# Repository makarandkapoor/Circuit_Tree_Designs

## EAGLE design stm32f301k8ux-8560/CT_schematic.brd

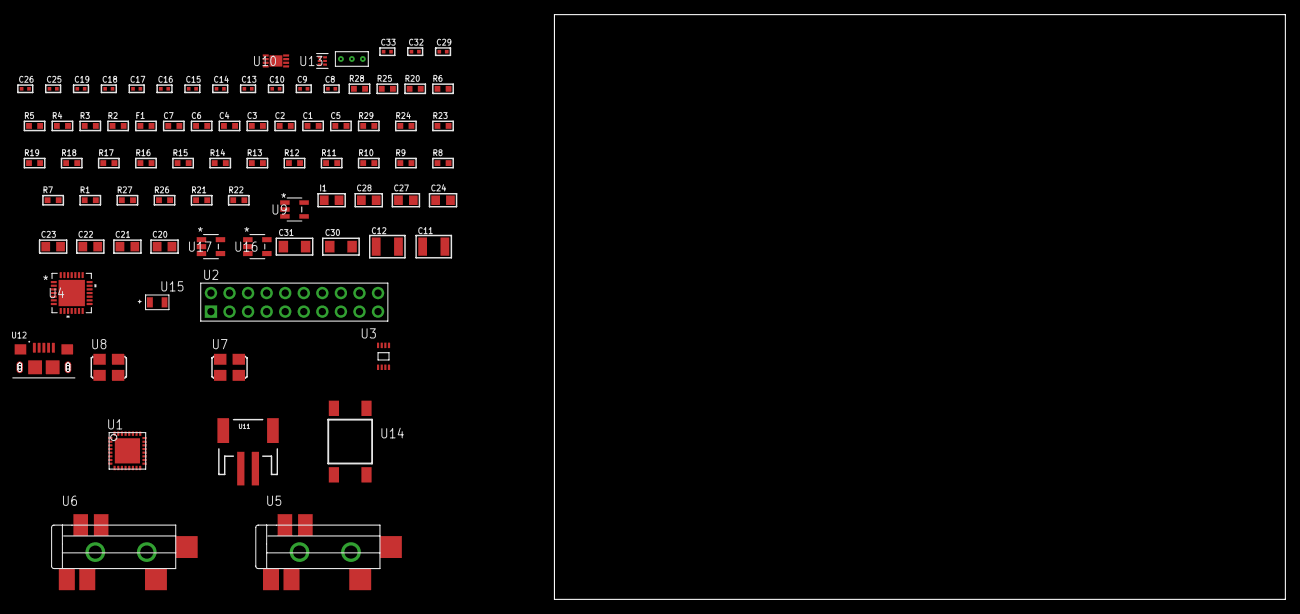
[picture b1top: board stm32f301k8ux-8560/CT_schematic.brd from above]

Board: 2 copper layers, 173.4 x 80.0 mm, 82 parts (0 on the bottom side), 41 nets, no tracks yet.

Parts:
C1, C2, C3, C4: 1e-07; C0603
C5: 4.7e-06; C0603
C6: 1e-08; C0603
C7: 1e-06; C0603
C8, C9, C15, C16, C17, C18, C19, C29: 1e-07; C0402
C10, C25, C26, C32, C33: 1e-08; C0402
C11, C12: 2.2e-05; C1210
C13, C14: 1e-09; C0402
C20, C21, C22, C23, C24, C27, C28: 1e-05; C0805
C30, C31: 1e-05; C1206
F1: 240.0; L0603
I1: 2.2e-06; L0805
R1, R7, R8, R9, R10, R11, R12, R13, R14, R15, R16, R23, R24, R29: 10000.0; R0603
R2: 1000.0; R0603
R3: 1600.5; R0603
R4: 4700.0; R0603
R5, R6: 2200.0; R0603
R17, R18, R19: 47000.0; R0603
R20: 680.0; R0603
R21: 220000.0; R0603
R22: 1000000.0; R0603
R25: 9100.0; R0603
R26: 680000.0; R0603
R27: 120000.0; R0603
R28: 2000.0; R0603
U1: STM32F301K8U7; UFQFPN32
U2: TST-110-05-T-D-RA
U3: 24AA64T-I/MNY; TDFN-8/6MM
U4: WM8731CLSEFL; QFN-28
U5, U6: SJ-43515TS-SMT-TR
U7: ASFL1-12.288MHZ-EC-T; ASFL1
U8: ASFL1-25MHZ-NCS; ASFL1
U9: ltc3406es5; TSOT-23-5
U10: MCP73831T-2ACI/MC; DFN8_2X3MC
U11: S2B-PH-SM4-TB(LF)(SN); JST-2-SMD
U12: 10118193-0001LF; FCI_10118193-0001LF
U13: TPS3895ADRYR; SON-6
U14: 4-1437565-2; SW_4-1437565-2
U15: Q65110A2395; LGM67K-G1J2-24-Z
U16, U17: nc7sz125m5x; NC7SZ125M5X
U18: Dummy; DUMMY_PACKAGE_174

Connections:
CLK_U1_2: U1.2, U8.3
CLK_U4_1: U4.1, U7.3
GND: C1.2, C2.2, C3.2, C4.2, C5.2, C6.2, C7.2, C8.2, C9.2, C10.2, C14.2, C15.2, C16.2, C17.2, C18.2, C19.2, C20.2, C21.2, C22.2, C23.2, C24.2, C25.2, C26.2, C27.2, C28.1, C28.2, C29.2, C30.2, C31.2, C32.2, C33.2, R2.2, R7.2, R13.2, R14.2, R15.2, R17.2, R18.2, R19.2, R21.2, R25.2, R27.2, R28.2, U1.6, U1.16, U1.32, U1.EPAD, U2.4, U2.6, U2.8, U2.10, U2.12, U2.14, U2.16, U2.18, U2.20, U3.4, U3.7, U4.4, U4.15, U4.19, U4.25, U4.26, U4.29, U5.1, U6.1, U7.2, U8.2, U9.2, U10.6, U10.9, U11.2, U12.5, U12.6, U12.7, U12.8, U12.9, U13.2, U15.C, U16.2, U16.3, U17.1, U17.3, U18.1
INPUT_USBPOWER_5V: C30.1, R29.2, U10.1, U10.2, U12.1
NET_U1_4: R4.1, U1.4, U17.4
NET_U1_5: C6.1, C7.1, F1.1, U1.5
NET_U1_22: R3.1, U1.22, U15.A
NET_U1_28: R1.1, U1.28, U14.3, U14.4
NET_U1_29: R5.1, U1.29, U3.6
NET_U1_30: R6.1, U1.30, U3.5
NET_U1_31: R7.1, U1.31
NET_U2_19: R13.1, U2.19
NET_U3_1: R14.1, U3.1
NET_U3_2: R15.1, U3.2
NET_U3_3: R16.1, U3.3
NET_U4_20: C19.1, C24.1, U4.20
NET_U5_2: C12.1, R18.1, U5.2
NET_U5_5: C11.1, R17.1, U5.5
NET_U6_5: C13.1, C14.1, R19.1, R20.1, U6.5
NET_U9_3: I1.1, U9.3
NET_U9_5: R21.1, R22.1, U9.5
NET_U9_ATNET_3: I1.2, R22.2
NET_U10_5: R29.1, U10.5
NET_U10_8: R28.1, U10.8
NET_U13_1: R24.1, R25.1, U13.1
NET_U13_3: R26.2, R27.1, U13.3
NET_U13_4: R23.1, U13.4, U16.4, U17.2
NET_U14_1: R2.1, U14.1, U14.2
PROC_ADC1_IN1: U1.7, U18.3
PROC_ADC1_IN2: U1.8, U18.2
PROC_I2S2_CK: U1.3, U4.7
PROC_I2S2_EXT_SD: U1.20, U4.10
PROC_I2S2_SD: U1.21, U4.8
PROC_SYS_JTCK_SWCLK: R11.1, U1.24, U2.9
PROC_SYS_JTDI: R9.1, U1.25, U2.5
PROC_SYS_JTDO_TRACESWO: U1.26, U2.13
PROC_SYS_JTMS_SWDIO: R10.1, U1.23, U2.7
PROC_SYS_NJTRST: R8.1, U1.27, U2.3
RST_OUT_U2_SRESET_B: R12.1, U2.15, U16.1
VCC_S1_3V7: C27.1, C31.1, U9.4, U10.3, U10.4, U11.1
VCC_TIER1_3V3: C1.1, C2.1, C3.1, C4.1, C5.1, C8.1, C9.1, C10.1, C15.1, C16.1, C17.1, C18.1, C20.1, C21.1, C22.1, C23.1, C25.1, C26.1, C28.2, C29.1, C32.1, C33.1, F1.2, I1.2, R1.2, R3.2, R4.2, R5.2, R6.2, R8.2, R9.2, R10.2, R11.2, R12.2, R16.2, R22.2, R23.2, R24.2, R26.1, U1.1, U1.17, U2.1, U2.2, U3.8, U4.3, U4.5, U4.12, U4.18, U7.4, U8.4, U13.6, U16.5, U17.5

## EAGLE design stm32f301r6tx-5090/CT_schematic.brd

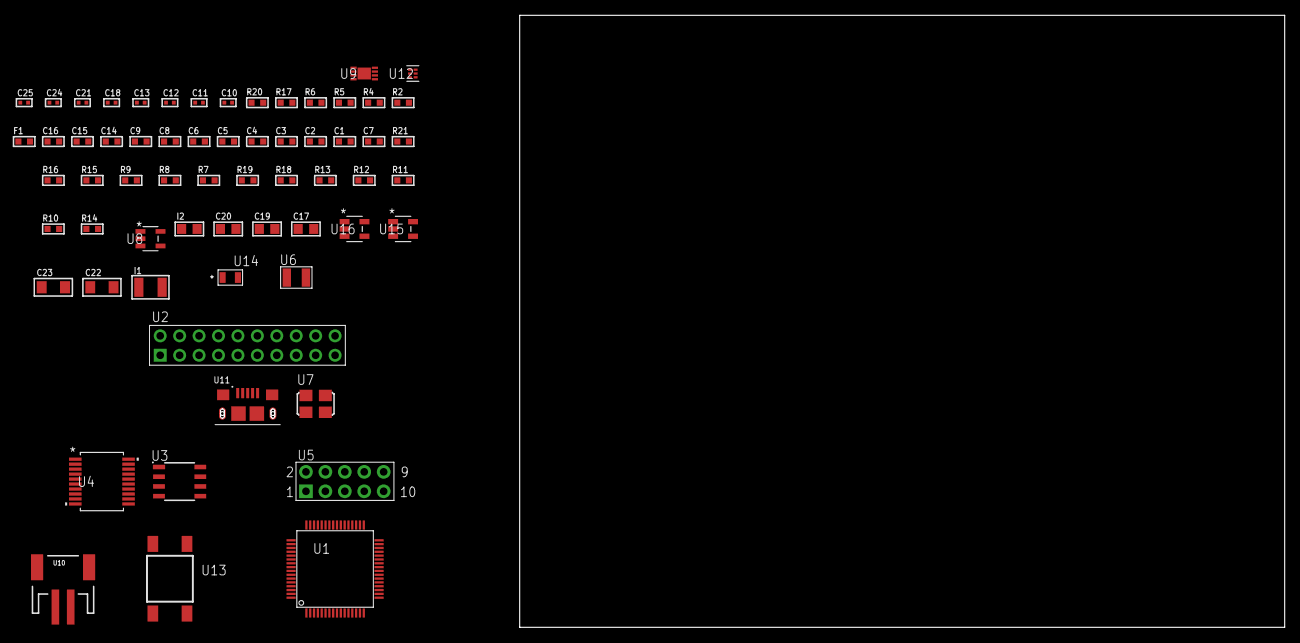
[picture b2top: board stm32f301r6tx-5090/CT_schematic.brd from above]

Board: 2 copper layers, 63 parts (0 on the bottom side), 43 nets, no tracks yet.

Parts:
C1, C9, C14, C15, C16: 1e-06; C0603
C2, C3, C4, C5, C6: 1e-07; C0603
C7: 4.7e-06; C0603
C8: 1e-08; C0603
C10, C11: 1e-11; C0402
C12, C21: 1e-07; C0402
C13, C18, C24, C25: 1e-08; C0402
C17: 4.7e-06; C0805
C19, C20: 1e-05; C0805
C22, C23: 1e-05; C1206
F1: 240.0; L0603
I1: 1.5e-05; L1210
I2: 2.2e-06; L0805
R2: 1000.0; R0603
R4: 4700.0; R0603
R5, R6: 2200.0; R0603
R7, R8, R9, R15, R16, R21: 10000.0; R0603
R10, R11, R12: 100000.0; R0603
R13: 220000.0; R0603
R14: 1000000.0; R0603
R17: 9100.0; R0603
R18: 680000.0; R0603
R19: 120000.0; R0603
R20: 2000.0; R0603
U1: STM32F301R6T6; LQFP64
U2: TST-110-05-T-D-RA
U3: M24M02-DRMN6TP; SOIC-8
U4: MAX3218EAP+T; SSOP-20
U5: HTSS-105-01-G-D
U6: ABS07-32.768KHZ-7-T
U7: ASFL1-25MHZ-NCS; ASFL1
U8: ltc3406es5; TSOT-23-5
U9: MCP73831T-2ACI/MC; DFN8_2X3MC
U10: S2B-PH-SM4-TB(LF)(SN); JST-2-SMD
U11: 10118193-0001LF; FCI_10118193-0001LF
U12: TPS3895ADRYR; SON-6
U13: 4-1437565-2; SW_4-1437565-2
U14: Q65110A2395; LGM67K-G1J2-24-Z
U15, U16: nc7sz125m5x; NC7SZ125M5X

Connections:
CLK_CRYSTAL_U1_3: C10.1, U1.3, U6.1
CLK_CRYSTAL_U1_4: C11.1, U1.4, U6.2
CLK_U1_5: U1.5, U7.3
GND: C1.2, C2.2, C3.2, C4.2, C5.2, C6.2, C7.2, C8.2, C9.2, C10.2, C11.2, C12.2, C13.2, C14.2, C15.2, C16.2, C18.2, C19.2, C20.1, C20.2, C21.2, C22.2, C23.2, C24.2, C25.2, R2.2, R7.2, R9.2, R13.2, R17.2, R19.2, R20.2, U1.12, U1.18, U1.31, U1.47, U1.63, U2.4, U2.6, U2.8, U2.10, U2.12, U2.14, U2.16, U2.18, U2.20, U3.4, U4.5, U4.17, U4.20, U5.9, U7.2, U8.2, U9.6, U9.9, U10.2, U11.5, U11.6, U11.7, U11.8, U11.9, U12.2, U14.C, U15.2, U15.3, U16.1, U16.3
INPUT_USBPOWER_5V: C22.1, R21.2, U9.1, U9.2, U11.1
NET_U1_7: R4.1, U1.7, U16.4
NET_U1_13: C8.1, C9.1, F1.1, U1.13
NET_U1_50: R5.1, U1.50, U3.6
NET_U1_59: R6.1, U1.59, U3.5
NET_U1_60: R7.1, U1.60
NET_U1_62: U13.3, U13.4
NET_U3_3: R9.1, U3.3
NET_U4_1: I1.1, U4.1
NET_U4_2: R10.1, U4.2
NET_U4_3: R11.1, U4.3
NET_U4_4: R12.1, U4.4
NET_U4_15: C16.1, U4.15
NET_U4_16: C17.2, U4.16
NET_U4_18: C17.1, U4.18
NET_U4_19: C15.1, U4.19
NET_U5_3: U4.12, U5.3
NET_U5_4: U4.11, U5.4
NET_U5_5: U4.14, U5.5
NET_U5_6: U4.13, U5.6
NET_U8_3: I2.1, U8.3
NET_U8_5: R13.1, R14.1, U8.5
NET_U8_ATNET_3: I2.2, R14.2
NET_U9_5: R21.1, U9.5
NET_U9_8: R20.1, U9.8
NET_U12_1: R16.1, R17.1, U12.1
NET_U12_3: R18.2, R19.1, U12.3
NET_U12_4: R15.1, U12.4, U15.4, U16.2
NET_U13_1: R2.1, U13.1, U13.2
PROC_SYS_JTCK_SWCLK: U1.49, U2.9
PROC_SYS_JTDO_TRACESWO: U1.55, U2.13
PROC_SYS_JTMS_SWDIO: U1.46, U2.7
PROC_USART1_CTS: U1.44, U4.8
PROC_USART1_RTS: U1.45, U4.10
PROC_USART1_RX: U1.25, U4.9
PROC_USART1_TX: U1.24, U4.7
RST_OUT_U2_SRESET_B: R8.1, U2.15, U15.1
VCC_S1_3V7: C19.1, C23.1, U8.4, U9.3, U9.4, U10.1
VCC_TIER1_3V3: C1.1, C2.1, C3.1, C4.1, C5.1, C6.1, C7.1, C12.1, C13.1, C14.1, C18.1, C20.2, C21.1, C24.1, C25.1, F1.2, I1.2, I2.2, R4.2, R5.2, R6.2, R8.2, R10.2, R11.2, R12.2, R14.2, R15.2, R16.2, R18.1, U1.1, U1.19, U1.32, U1.48, U1.64, U2.1, U3.8, U4.6, U7.4, U12.6, U15.5, U16.5

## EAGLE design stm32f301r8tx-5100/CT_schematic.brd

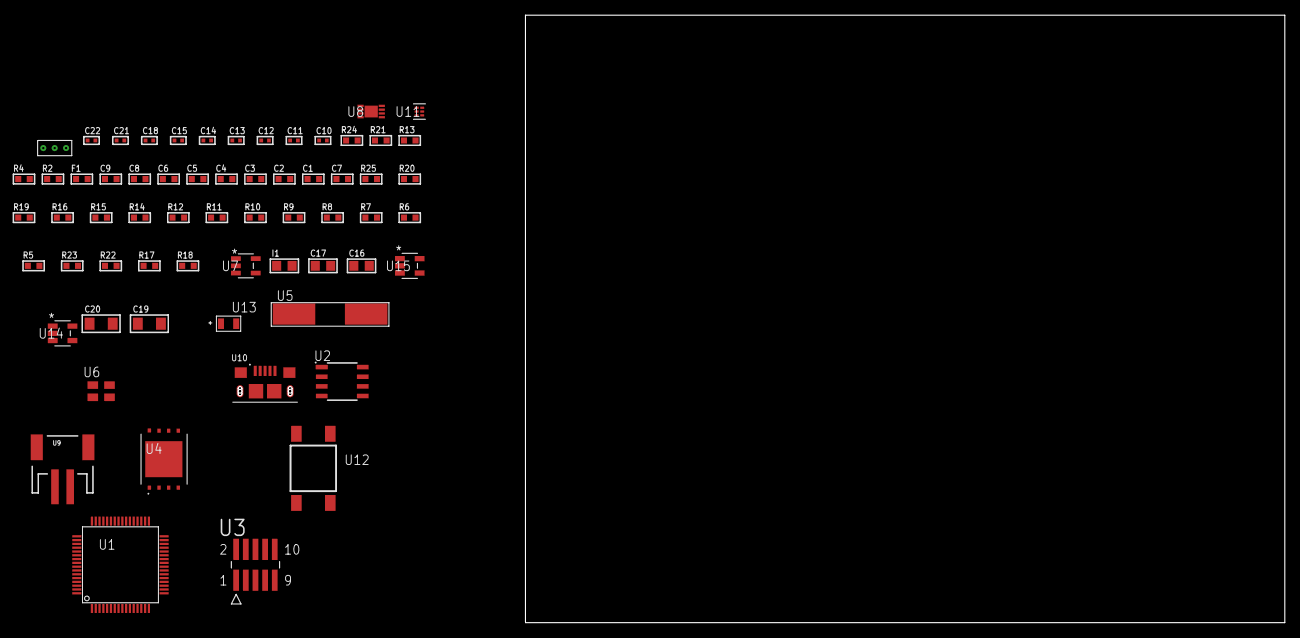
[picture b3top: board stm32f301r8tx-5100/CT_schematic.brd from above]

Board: 2 copper layers, 63 parts (0 on the bottom side), 40 nets, no tracks yet.

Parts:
C1, C9: 1e-06; C0603
C2, C3, C4, C5, C6: 1e-07; C0603
C7: 4.7e-06; C0603
C8: 1e-08; C0603
C10, C11: 1e-11; C0402
C12, C14, C15, C21, C22: 1e-08; C0402
C13, C18: 1e-07; C0402
C16, C17: 1e-05; C0805
C19, C20: 1e-05; C1206
F1: 240.0; L0603
I1: 2.2e-06; L0805
R2: 1000.0; R0603
R4: 4700.0; R0603
R5, R6, R7, R8, R9, R10, R11, R12, R14, R15, R16, R19, R20, R25: 10000.0; R0603
R13: 5.0; R0603
R17: 220000.0; R0603
R18: 1000000.0; R0603
R21: 9100.0; R0603
R22: 680000.0; R0603
R23: 120000.0; R0603
R24: 2000.0; R0603
U1: STM32F301R8T6; LQFP64
U2: AT25160B-SSHL-T; SOIC-8
U3: FTSH-105-01-L-DV-K; SAMTEC_FTSH-105-01-L-DV-K
U4: S25FL128SDPNFI001; WNG008
U5: ABLS-25.000MHZ-B2F-T
U6: ASEK-32.768KHz-ECST; ASEK
U7: ltc3406es5; TSOT-23-5
U8: MCP73831T-2ACI/MC; DFN8_2X3MC
U9: S2B-PH-SM4-TB(LF)(SN); JST-2-SMD
U10: 10118193-0001LF; FCI_10118193-0001LF
U11: TPS3895ADRYR; SON-6
U12: 4-1437565-2; SW_4-1437565-2
U13: Q65110A2395; LGM67K-G1J2-24-Z
U14, U15: nc7sz125m5x; NC7SZ125M5X
U16: Dummy; DUMMY_PACKAGE_137

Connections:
CLK_CRYSTAL_U1_5: C10.1, U1.5, U5.1
CLK_CRYSTAL_U1_6: C11.1, U1.6, U5.2
CLK_U1_3: U1.3, U6.3
GND: C1.2, C2.2, C3.2, C4.2, C5.2, C6.2, C7.2, C8.2, C9.2, C10.2, C11.2, C12.2, C13.2, C14.2, C15.2, C16.2, C17.1, C17.2, C18.2, C19.2, C20.2, C21.2, C22.2, R2.2, R5.2, R12.2, R13.2, R17.2, R21.2, R23.2, R24.2, U1.12, U1.18, U1.31, U1.47, U1.63, U2.4, U3.3, U3.5, U4.4, U4.PAD, U6.2, U7.2, U8.6, U8.9, U9.2, U10.5, U10.6, U10.7, U10.8, U10.9, U11.2, U13.C, U14.2, U14.3, U15.1, U15.3, U16.1
INPUT_USBPOWER_5V: C19.1, R25.2, U8.1, U8.2, U10.1
NET_U1_7: R4.1, U1.7, U15.4
NET_U1_13: C8.1, C9.1, F1.1, U1.13
NET_U1_60: R5.1, U1.60
NET_U1_62: U12.3, U12.4
NET_U2_3: R6.1, U2.3
NET_U2_7: R8.1, U2.7
NET_U3_9: R13.1, U3.9
NET_U4_3: R14.1, U4.3
NET_U4_7: R16.1, U4.7
NET_U7_3: I1.1, U7.3
NET_U7_5: R17.1, R18.1, U7.5
NET_U7_ATNET_3: I1.2, R18.2
NET_U8_5: R25.1, U8.5
NET_U8_8: R24.1, U8.8
NET_U11_1: R20.1, R21.1, U11.1
NET_U11_3: R22.2, R23.1, U11.3
NET_U11_4: R19.1, U11.4, U14.4, U15.2
NET_U12_1: R2.1, U12.1, U12.2
PROC_SPI2_MISO: U1.35, U4.2
PROC_SPI2_MOSI: U1.36, U4.5
PROC_SPI2_NSS: R15.1, U1.33, U4.1
PROC_SPI2_SCK: U1.34, U4.6
PROC_SPI3_MISO: U1.52, U2.2
PROC_SPI3_MOSI: U1.53, U2.5
PROC_SPI3_NSS: R7.1, U1.20, U2.1
PROC_SPI3_SCK: U1.51, U2.6
PROC_SYS_JTCK_SWCLK: R12.1, U1.49, U3.4
PROC_SYS_JTDI: R10.1, U1.50, U3.8
PROC_SYS_JTDO_TRACESWO: U1.55, U3.6
PROC_SYS_JTMS_SWDIO: R11.1, U1.46, U3.2
PROC_TIM1_CH2: U1.9, U16.2
PROC_TIM1_CH4: U1.11, U16.3
RST_OUT_U3_JTAG_RST_B: R9.1, U3.10, U14.1
VCC_S1_3V7: C16.1, C20.1, U7.4, U8.3, U8.4, U9.1
VCC_TIER1_3V3: C1.1, C2.1, C3.1, C4.1, C5.1, C6.1, C7.1, C12.1, C13.1, C14.1, C15.1, C17.2, C18.1, C21.1, C22.1, F1.2, I1.2, R4.2, R6.2, R7.2, R8.2, R9.2, R10.2, R11.2, R14.2, R15.2, R16.2, R18.2, R19.2, R20.2, R22.1, U1.1, U1.19, U1.32, U1.48, U1.64, U2.8, U3.1, U4.8, U6.4, U11.6, U14.5, U15.5

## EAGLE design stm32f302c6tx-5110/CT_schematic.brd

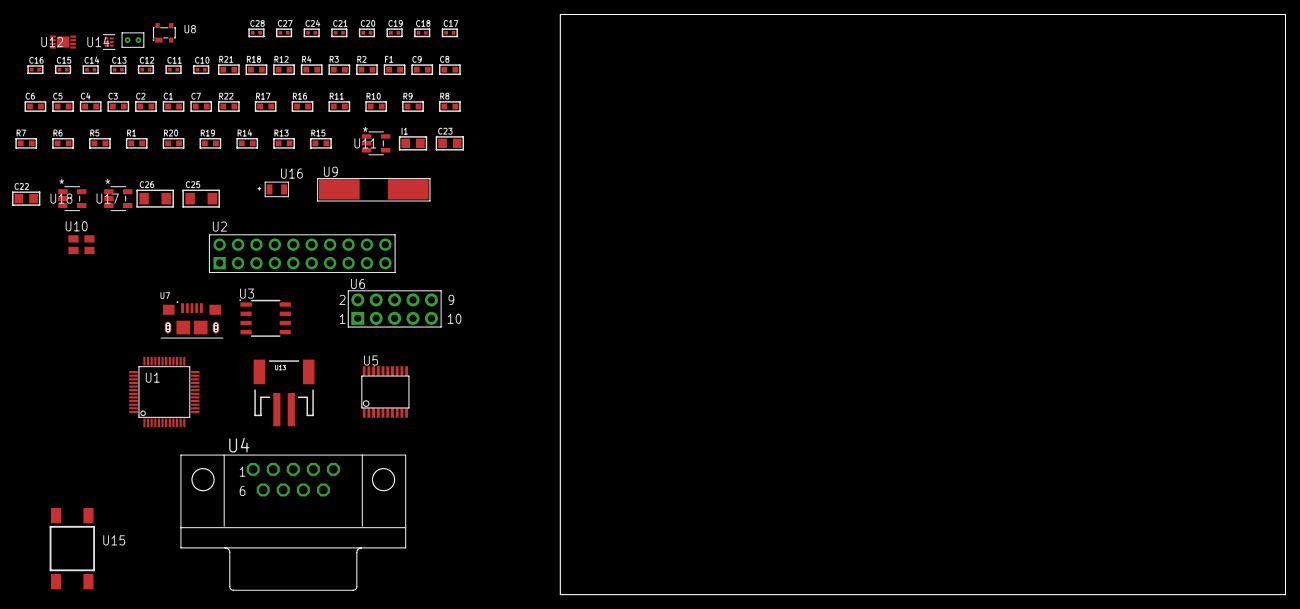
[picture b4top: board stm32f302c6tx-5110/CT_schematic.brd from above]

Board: 2 copper layers, 71 parts (0 on the bottom side), 51 nets, no tracks yet.

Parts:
C1, C9: 1e-06; C0603
C2, C3, C4, C5, C6: 1e-07; C0603
C7: 4.7e-06; C0603
C8: 1e-08; C0603
C10, C11: 1e-11; C0402
C12, C13, C14, C15, C16, C17, C18, C19, C20, C24: 1e-07; C0402
C21, C27, C28: 1e-08; C0402
C22, C23: 1e-05; C0805
C25, C26: 1e-05; C1206
F1: 240.0; L0603
I1: 2.2e-06; L0805
R1, R5, R6, R7, R8, R9, R10, R11, R16, R17, R22: 10000.0; R0603
R2: 1000.0; R0603
R3: 1600.5; R0603
R4: 4700.0; R0603
R12: 120.0; R0603
R13: 100000.0; R0603
R14: 220000.0; R0603
R15: 1000000.0; R0603
R18: 9100.0; R0603
R19: 680000.0; R0603
R20: 120000.0; R0603
R21: 2000.0; R0603
U1: STM32F302C6T6; LQFP48
U2: TST-110-05-T-D-RA
U3: SN65HVD230D; SOIC-8
U4: 182-009-113R531; 182-009-MALE
U5: SP3203ECY-L/TR; TSSOP20-I
U6: HTSS-105-01-G-D
U7: 10118193-0001LF; FCI_10118193-0001LF
U8: prtr5v0u2ax; SOT143B
U9: ABLS-25.000MHZ-B2F-T
U10: ASEK-32.768KHz-ECST; ASEK
U11: ltc3406es5; TSOT-23-5
U12: MCP73831T-2ACI/MC; DFN8_2X3MC
U13: S2B-PH-SM4-TB(LF)(SN); JST-2-SMD
U14: TPS3895ADRYR; SON-6
U15: 4-1437565-2; SW_4-1437565-2
U16: Q65110A2395; LGM67K-G1J2-24-Z
U17, U18: nc7sz125m5x; NC7SZ125M5X
U19: Dummy; DUMMY_PACKAGE_149

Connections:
CLK_CRYSTAL_U1_5: C10.1, U1.5, U9.1
CLK_CRYSTAL_U1_6: C11.1, U1.6, U9.2
CLK_U1_3: U1.3, U10.3
GND: C1.2, C2.2, C3.2, C4.2, C5.2, C6.2, C7.2, C8.2, C9.2, C10.2, C11.2, C12.2, C13.2, C14.2, C15.2, C16.2, C19.2, C20.2, C21.2, C22.2, C23.1, C23.2, C24.2, C25.2, C26.2, C27.2, C28.2, R2.2, R5.2, R11.2, R13.2, R14.2, R18.2, R20.2, R21.2, U1.8, U1.23, U1.35, U1.47, U2.4, U2.6, U2.8, U2.10, U2.12, U2.14, U2.16, U2.18, U2.20, U3.2, U4.5, U5.18, U6.9, U7.5, U7.6, U7.7, U7.8, U7.9, U8.1, U10.2, U11.2, U12.6, U12.9, U13.2, U14.2, U16.C, U17.2, U17.3, U18.1, U18.3, U19.1
INPUT_USBPOWER_5V: C25.1, R22.2, U7.1, U8.4, U12.1, U12.2
NET_U1_7: R4.1, U1.7, U18.4
NET_U1_9: C8.1, C9.1, F1.1, U1.9
NET_U1_42: R3.1, U1.42, U16.A
NET_U1_43: R1.1, U1.43, U15.3, U15.4
NET_U1_44: R5.1, U1.44
NET_U2_19: R11.1, U2.19
NET_U3_6: R12.2, U3.6
NET_U3_8: R13.1, U3.8
NET_U4_2: R12.2, U3.6, U4.2
NET_U4_3: R12.1, U3.7, U4.3
NET_U5_1: C17.1, U5.1
NET_U5_2: C19.1, U5.2
NET_U5_3: C17.2, U5.3
NET_U5_4: C18.1, U5.4
NET_U5_5: C18.2, U5.5
NET_U5_6: C20.1, U5.6
NET_U6_3: U5.14, U6.3
NET_U6_4: U5.13, U6.4
NET_U6_5: U5.17, U6.5
NET_U6_6: U5.16, U6.6
NET_U11_3: I1.1, U11.3
NET_U11_5: R14.1, R15.1, U11.5
NET_U11_ATNET_3: I1.2, R15.2
NET_U12_5: R22.1, U12.5
NET_U12_8: R21.1, U12.8
NET_U14_1: R17.1, R18.1, U14.1
NET_U14_3: R19.2, R20.1, U14.3
NET_U14_4: R16.1, U14.4, U17.4, U18.2
NET_U15_1: R2.1, U15.1, U15.2
PROC_CAN_RX: U1.45, U3.4
PROC_CAN_TX: U1.46, U3.1
PROC_DAC_OUT1: U1.14, U19.2
PROC_SYS_JTCK_SWCLK: R9.1, U1.37, U2.9
PROC_SYS_JTDI: R7.1, U1.38, U2.5
PROC_SYS_JTDO_TRACESWO: U1.39, U2.13
PROC_SYS_JTMS_SWDIO: R8.1, U1.34, U2.7
PROC_SYS_NJTRST: R6.1, U1.40, U2.3
PROC_USART2_CTS: U1.10, U5.8
PROC_USART2_RTS: U1.11, U5.10
PROC_USART2_RX: U1.13, U5.11
PROC_USART2_TX: U1.12, U5.7
PROC_USB_DM: U1.32, U7.2, U8.3
PROC_USB_DP: U1.33, U7.3, U8.2
RST_OUT_U2_SRESET_B: R10.1, U2.15, U17.1
VCC_S1_3V7: C22.1, C26.1, U11.4, U12.3, U12.4, U13.1
VCC_TIER1_3V3: C1.1, C2.1, C3.1, C4.1, C5.1, C6.1, C7.1, C12.1, C13.1, C14.1, C15.1, C16.1, C21.1, C23.2, C24.1, C27.1, C28.1, F1.2, I1.2, R1.2, R3.2, R4.2, R6.2, R7.2, R8.2, R9.2, R10.2, R15.2, R16.2, R17.2, R19.1, U1.1, U1.24, U1.36, U1.48, U2.1, U2.2, U3.3, U5.12, U5.19, U10.4, U14.6, U17.5, U18.5

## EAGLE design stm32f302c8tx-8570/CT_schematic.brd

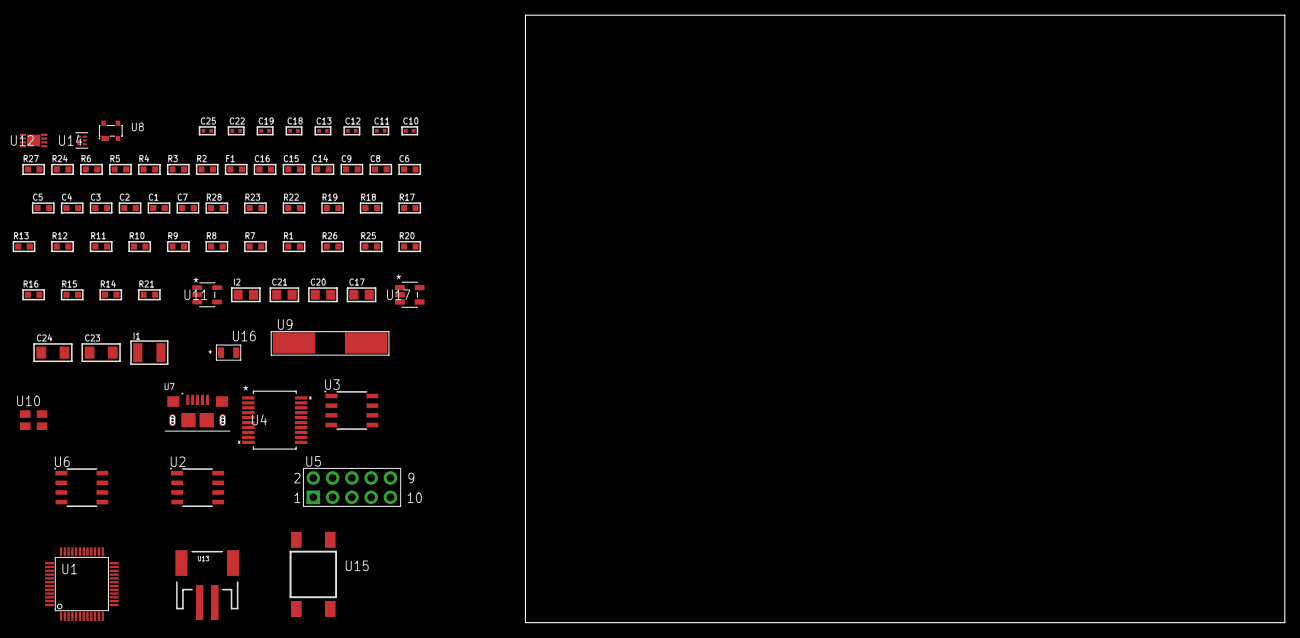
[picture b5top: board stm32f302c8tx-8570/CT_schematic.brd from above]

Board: 2 copper layers, 73 parts (0 on the bottom side), 56 nets, no tracks yet.

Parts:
C1, C9, C14, C15, C16: 1e-06; C0603
C2, C3, C4, C5, C6: 1e-07; C0603
C7: 4.7e-06; C0603
C8: 1e-08; C0603
C10, C11: 1e-11; C0402
C12, C13, C18, C19, C25: 1e-08; C0402
C17: 4.7e-06; C0805
C20, C21: 1e-05; C0805
C22: 1e-07; C0402
C23, C24: 1e-05; C1206
F1: 240.0; L0603
I1: 1.5e-05; L1210
I2: 2.2e-06; L0805
R1, R7, R8, R9, R10, R11, R12, R13, R17, R18, R19, R22, R23, R28: 10000.0; R0603
R2: 1000.0; R0603
R3: 1600.5; R0603
R4: 4700.0; R0603
R5, R6: 2200.0; R0603
R14, R15, R16: 100000.0; R0603
R20: 220000.0; R0603
R21: 1000000.0; R0603
R24: 9100.0; R0603
R25: 680000.0; R0603
R26: 120000.0; R0603
R27: 2000.0; R0603
U1: STM32F302C8T7; LQFP48
U2: AT25128B-SSHL-T; SOIC-8
U3: AT25512N-SH-T; SOIC-8
U4: MAX3218EAP+T; SSOP-20
U5: HTSS-105-01-G-D
U6: 24AA1025T-I/SN; SOIC-8
U7: 10118193-0001LF; FCI_10118193-0001LF
U8: prtr5v0u2ax; SOT143B
U9: ABLS-25.000MHZ-B2F-T
U10: ASEK-32.768KHz-ECST; ASEK
U11: ltc3406es5; TSOT-23-5
U12: MCP73831T-2ACI/MC; DFN8_2X3MC
U13: S2B-PH-SM4-TB(LF)(SN); JST-2-SMD
U14: TPS3895ADRYR; SON-6
U15: 4-1437565-2; SW_4-1437565-2
U16: Q65110A2395; LGM67K-G1J2-24-Z
U17: nc7sz125m5x; NC7SZ125M5X

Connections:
CLK_CRYSTAL_U1_5: C10.1, U1.5, U9.1
CLK_CRYSTAL_U1_6: C11.1, U1.6, U9.2
CLK_U1_3: U1.3, U10.3
GND: C1.2, C2.2, C3.2, C4.2, C5.2, C6.2, C7.2, C8.2, C9.2, C10.2, C11.2, C12.2, C13.2, C14.2, C15.2, C16.2, C18.2, C19.2, C20.2, C21.1, C21.2, C22.2, C23.2, C24.2, C25.2, R2.2, R7.2, R20.2, R24.2, R26.2, R27.2, U1.8, U1.23, U1.35, U1.47, U2.4, U3.4, U4.5, U4.17, U4.20, U5.9, U6.4, U7.5, U7.6, U7.7, U7.8, U7.9, U8.1, U10.2, U11.2, U12.6, U12.9, U13.2, U14.2, U16.C, U17.1, U17.3
INPUT_USBPOWER_5V: C23.1, R28.2, U7.1, U8.4, U12.1, U12.2
NET_U1_7: R4.1, U1.7, U17.4
NET_U1_9: C8.1, C9.1, F1.1, U1.9
NET_U1_37: R6.1, U1.37, U6.5
NET_U1_38: R5.1, U1.38, U6.6
NET_U1_44: R7.1, U1.44
NET_U1_45: R3.1, U1.45, U16.A
NET_U1_46: R1.1, U1.46, U15.3, U15.4
NET_U2_3: R8.1, U2.3
NET_U2_7: R10.1, U2.7
NET_U3_3: R11.1, U3.3
NET_U3_7: R13.1, U3.7
NET_U4_1: I1.1, U4.1
NET_U4_2: R14.1, U4.2
NET_U4_3: R15.1, U4.3
NET_U4_4: R16.1, U4.4
NET_U4_15: C16.1, U4.15
NET_U4_16: C17.2, U4.16
NET_U4_18: C17.1, U4.18
NET_U4_19: C15.1, U4.19
NET_U5_3: U4.12, U5.3
NET_U5_4: U4.11, U5.4
NET_U5_5: U4.14, U5.5
NET_U5_6: U4.13, U5.6
NET_U6_1: R18.1, U6.1
NET_U6_2: R19.1, U6.2
NET_U6_3: R17.1, U6.3
NET_U11_3: I2.1, U11.3
NET_U11_5: R20.1, R21.1, U11.5
NET_U11_ATNET_3: I2.2, R21.2
NET_U12_5: R28.1, U12.5
NET_U12_8: R27.1, U12.8
NET_U14_1: R23.1, R24.1, U14.1
NET_U14_3: R25.2, R26.1, U14.3
NET_U14_4: R22.1, U14.4, U17.2
NET_U15_1: R2.1, U15.1, U15.2
PROC_SPI2_MISO: U1.27, U3.2
PROC_SPI2_MOSI: U1.28, U3.5
PROC_SPI2_NSS: R12.1, U1.25, U3.1
PROC_SPI2_SCK: U1.26, U3.6
PROC_SPI3_MISO: U1.40, U2.2
PROC_SPI3_MOSI: U1.41, U2.5
PROC_SPI3_NSS: R9.1, U1.14, U2.1
PROC_SPI3_SCK: U1.39, U2.6
PROC_USART2_CTS: U1.10, U4.8
PROC_USART2_RTS: U1.11, U4.10
PROC_USART2_RX: U1.13, U4.9
PROC_USART2_TX: U1.12, U4.7
PROC_USB_DM: U1.32, U7.2, U8.3
PROC_USB_DP: U1.33, U7.3, U8.2
VCC_S1_3V7: C20.1, C24.1, U11.4, U12.3, U12.4, U13.1
VCC_TIER1_3V3: C1.1, C2.1, C3.1, C4.1, C5.1, C6.1, C7.1, C12.1, C13.1, C14.1, C18.1, C19.1, C21.2, C22.1, C25.1, F1.2, I1.2, I2.2, R1.2, R3.2, R4.2, R5.2, R6.2, R8.2, R9.2, R10.2, R11.2, R12.2, R13.2, R14.2, R15.2, R16.2, R17.2, R18.2, R19.2, R21.2, R22.2, R23.2, R25.1, U1.1, U1.24, U1.36, U1.48, U2.8, U3.8, U4.6, U6.7, U6.8, U10.4, U14.6, U17.5

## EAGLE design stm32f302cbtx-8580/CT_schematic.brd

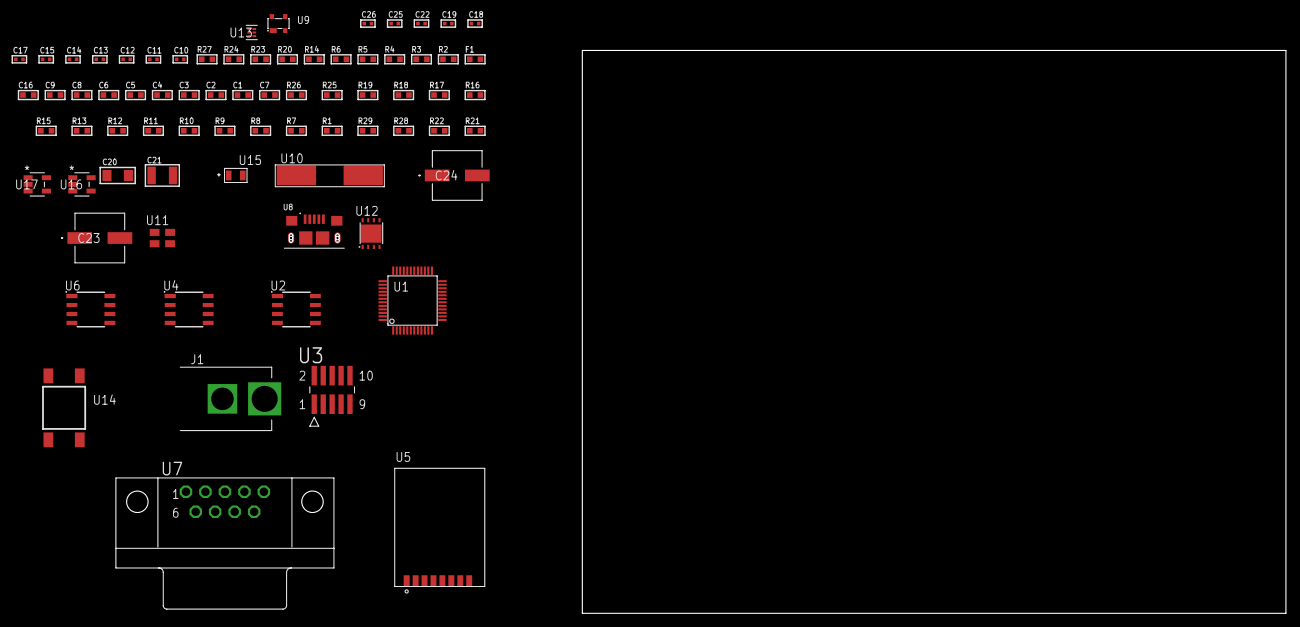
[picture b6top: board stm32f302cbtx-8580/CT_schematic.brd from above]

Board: 2 copper layers, 74 parts (0 on the bottom side), 48 nets, no tracks yet.

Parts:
C1, C9, C16: 1e-06; C0603
C2, C3, C4, C5, C6: 1e-07; C0603
C7: 4.7e-06; C0603
C8: 1e-08; C0603
C10, C11: 1e-11; C0402
C12, C14, C18, C19, C25, C26: 1e-08; C0402
C13, C15, C17, C22: 1e-07; C0402
C20: 1e-05; C1206
C21: 1e-05; C1210
C23, C24: 0.0001; EXV-9H
F1: 240.0; L0603
J1: PJ-037B; PJ-037B_PACKAGE
R1, R7, R8, R9, R10, R11, R12, R13, R15, R16, R17, R18, R19, R25, R26: 10000.0; R0603
R2, R24: 1000.0; R0603
R3: 1600.5; R0603
R4: 4700.0; R0603
R5, R6: 2200.0; R0603
R14: 5.0; R0603
R20: 120.0; R0603
R21: 470000.0; R0603
R22: 100000.0; R0603
R23: 2231.0; R0603
R27: 9100.0; R0603
R28: 680000.0; R0603
R29: 120000.0; R0603
U1: STM32F302CBT6; LQFP48
U2: AT25040B-SSHL-T; SOIC-8
U3: FTSH-105-01-L-DV-K; SAMTEC_FTSH-105-01-L-DV-K
U4: 24AA1025T-I/SN; SOIC-8
U5: RFM75-S
U6: SN65HVD230D; SOIC-8
U7: 182-009-113R531; 182-009-MALE
U8: 10118193-0001LF; FCI_10118193-0001LF
U9: prtr5v0u2ax; SOT143B
U10: ABLS-25.000MHZ-B2F-T
U11: ASEK-32.768KHz-ECST; ASEK
U12: LP3878SDX-ADJ/NOPB; WSON-8
U13: TPS3895ADRYR; SON-6
U14: 4-1437565-2; SW_4-1437565-2
U15: Q65110A2395; LGM67K-G1J2-24-Z
U16, U17: nc7sz125m5x; NC7SZ125M5X

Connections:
CLK_CRYSTAL_U1_5: C10.1, U1.5, U10.1
CLK_CRYSTAL_U1_6: C11.1, U1.6, U10.2
CLK_U1_3: U1.3, U11.3
GND: C1.2, C2.2, C3.2, C4.2, C5.2, C6.2, C7.2, C8.2, C9.2, C10.2, C11.2, C12.2, C13.2, C14.2, C15.2, C16.2, C17.2, C18.2, C19.2, C20.2, C21.2, C22.2, C23.2, C24.2, C25.2, C26.2, J1.2, R2.2, R7.2, R14.2, R21.2, R24.2, R27.2, R29.2, U1.8, U1.23, U1.35, U1.47, U2.4, U3.3, U3.5, U4.4, U5.1, U6.2, U7.5, U8.5, U8.6, U8.7, U8.8, U8.9, U9.1, U11.2, U12.3, U12.PAD, U13.2, U15.C, U16.2, U16.3, U17.1, U17.3
NET_U1_7: R4.1, U1.7, U17.4
NET_U1_9: C8.1, C9.1, F1.1, U1.9
NET_U1_38: R5.1, U1.38, U4.6
NET_U1_41: R3.1, U1.41, U15.A
NET_U1_42: R1.1, U1.42, U14.3, U14.4
NET_U1_43: R6.1, U1.43, U4.5
NET_U1_44: R7.1, U1.44
NET_U2_3: R8.1, U2.3
NET_U2_7: R10.1, U2.7
NET_U3_9: R14.1, U3.9
NET_U4_1: R16.1, U4.1
NET_U4_2: R17.1, U4.2
NET_U4_3: R15.1, U4.3
NET_U5_3: R18.1, U5.3
NET_U6_6: R20.2, U6.6
NET_U6_8: R21.1, U6.8
NET_U7_2: R20.2, U6.6, U7.2
NET_U7_3: R20.1, U6.7, U7.3
NET_U9_4: U8.1, U9.4
NET_U12_1: C19.1, U12.1
NET_U12_6: R23.2, R24.1, U12.6
NET_U12_8: R22.1, U12.8
NET_U13_1: R26.1, R27.1, U13.1
NET_U13_3: R28.2, R29.1, U13.3
NET_U13_4: R25.1, U13.4, U16.4, U17.2
NET_U14_1: R2.1, U14.1, U14.2
PROC_CAN_RX: U1.45, U6.4
PROC_CAN_TX: U1.46, U6.1
PROC_SPI1_MISO: U1.16, U5.7
PROC_SPI1_MOSI: U1.17, U5.6
PROC_SPI1_NSS: R19.1, U1.14, U5.4
PROC_SPI1_SCK: U1.15, U5.5
PROC_SPI2_MISO: U1.27, U2.2
PROC_SPI2_MOSI: U1.28, U2.5
PROC_SPI2_NSS: R9.1, U1.25, U2.1
PROC_SPI2_SCK: U1.26, U2.6
PROC_SYS_JTCK_SWCLK: R12.1, U1.37, U3.4
PROC_SYS_JTDO_TRACESWO: U1.39, U3.6
PROC_SYS_JTMS_SWDIO: R13.1, U1.34, U3.2
PROC_USB_DM: U1.32, U8.2, U9.3
PROC_USB_DP: U1.33, U8.3, U9.2
RST_OUT_U3_JTAG_RST_B: R11.1, U3.10, U16.1
VCC_S1_11V0: C20.1, C23.1, C24.1, J1.1, R22.2, U12.4
VCC_TIER1_3V3: C1.1, C2.1, C3.1, C4.1, C5.1, C6.1, C7.1, C12.1, C13.1, C14.1, C15.1, C16.1, C17.1, C18.1, C21.1, C22.1, C25.1, C26.1, F1.2, R1.2, R3.2, R4.2, R5.2, R6.2, R8.2, R9.2, R10.2, R11.2, R12.2, R13.2, R15.2, R16.2, R17.2, R18.2, R19.2, R23.1, R25.2, R26.2, R28.1, U1.1, U1.24, U1.36, U1.48, U2.8, U3.1, U4.7, U4.8, U5.2, U6.3, U11.4, U12.5, U13.6, U16.5, U17.5

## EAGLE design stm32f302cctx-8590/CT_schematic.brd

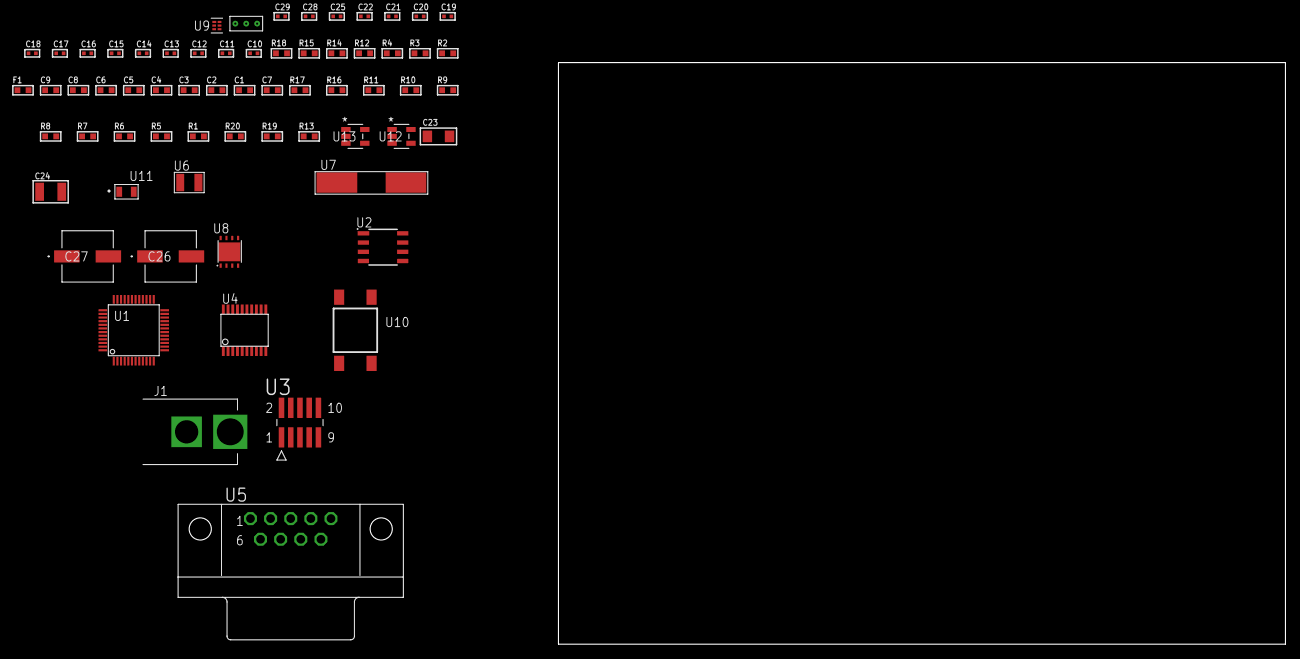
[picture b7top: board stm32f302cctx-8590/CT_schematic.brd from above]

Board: 2 copper layers, 100.0 x 80.0 mm, 65 parts (0 on the bottom side), 46 nets, no tracks yet.

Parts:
C1, C9: 1e-06; C0603
C2, C3, C4, C5, C6: 1e-07; C0603
C7: 4.7e-06; C0603
C8: 1e-08; C0603
C10, C11, C12, C13: 1e-11; C0402
C14, C22, C28, C29: 1e-08; C0402
C15, C16, C17, C18, C19, C20, C21, C25: 1e-07; C0402
C23: 1e-05; C1206
C24: 1e-05; C1210
C26, C27: 0.0001; EXV-9H
F1: 240.0; L0603
J1: PJ-037B; PJ-037B_PACKAGE
R1, R5, R6, R7, R8, R9, R10, R11, R16, R17: 10000.0; R0603
R2, R15: 1000.0; R0603
R3: 1600.5; R0603
R4: 4700.0; R0603
R12: 5.0; R0603
R13: 100000.0; R0603
R14: 2231.0; R0603
R18: 9100.0; R0603
R19: 680000.0; R0603
R20: 120000.0; R0603
U1: STM32F302CCT7; LQFP48
U2: AT25640B-SSHL-T; SOIC-8
U3: FTSH-105-01-L-DV-K; SAMTEC_FTSH-105-01-L-DV-K
U4: SP3203ECY-L/TR; TSSOP20-I
U5: 182-009-113R531; 182-009-MALE
U6: ABS07-32.768KHZ-7-T
U7: ABLS-25.000MHZ-B2F-T
U8: LP3878SDX-ADJ/NOPB; WSON-8
U9: TPS3895ADRYR; SON-6
U10: 4-1437565-2; SW_4-1437565-2
U11: Q65110A2395; LGM67K-G1J2-24-Z
U12, U13: nc7sz125m5x; NC7SZ125M5X
U14: Dummy; DUMMY_PACKAGE_132

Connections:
CLK_CRYSTAL_U1_3: C10.1, U1.3, U6.1
CLK_CRYSTAL_U1_4: C11.1, U1.4, U6.2
CLK_CRYSTAL_U1_5: C12.1, U1.5, U7.1
CLK_CRYSTAL_U1_6: C13.1, U1.6, U7.2
GND: C1.2, C2.2, C3.2, C4.2, C5.2, C6.2, C7.2, C8.2, C9.2, C10.2, C11.2, C12.2, C13.2, C14.2, C15.2, C16.2, C17.2, C20.2, C21.2, C22.2, C23.2, C24.2, C25.2, C26.2, C27.2, C28.2, C29.2, J1.2, R2.2, R5.2, R12.2, R15.2, R18.2, R20.2, U1.8, U1.23, U1.35, U1.47, U2.4, U3.3, U3.5, U4.18, U5.5, U8.3, U8.PAD, U9.2, U11.C, U12.2, U12.3, U13.1, U13.3, U14.1
NET_U1_7: R4.1, U1.7, U13.4
NET_U1_9: C8.1, C9.1, F1.1, U1.9
NET_U1_44: R5.1, U1.44
NET_U1_45: R3.1, U1.45, U11.A
NET_U1_46: R1.1, U1.46, U10.3, U10.4
NET_U2_3: R6.1, U2.3
NET_U2_7: R8.1, U2.7
NET_U3_9: R12.1, U3.9
NET_U4_1: C18.1, U4.1
NET_U4_2: C20.1, U4.2
NET_U4_3: C18.2, U4.3
NET_U4_4: C19.1, U4.4
NET_U4_5: C19.2, U4.5
NET_U4_6: C21.1, U4.6
NET_U5_2: U4.14, U5.2
NET_U5_3: U4.17, U5.3
NET_U5_7: U4.13, U5.7
NET_U5_8: U4.16, U5.8
NET_U8_1: C22.1, U8.1
NET_U8_6: R14.2, R15.1, U8.6
NET_U8_8: R13.1, U8.8
NET_U9_1: R17.1, R18.1, U9.1
NET_U9_3: R19.2, R20.1, U9.3
NET_U9_4: R16.1, U9.4, U12.4, U13.2
NET_U10_1: R2.1, U10.1, U10.2
PROC_SPI1_MISO: U1.16, U2.2
PROC_SPI1_MOSI: U1.17, U2.5
PROC_SPI1_NSS: R7.1, U1.14, U2.1
PROC_SPI1_SCK: U1.15, U2.6
PROC_SYS_JTCK_SWCLK: R10.1, U1.37, U3.4
PROC_SYS_JTDO_TRACESWO: U1.39, U3.6
PROC_SYS_JTMS_SWDIO: R11.1, U1.34, U3.2
PROC_TIM1_CH1: U1.29, U14.3
PROC_TIM1_CH2N: U1.18, U14.2
PROC_USART1_CTS: U1.32, U4.8
PROC_USART1_RTS: U1.33, U4.10
PROC_USART1_RX: U1.31, U4.11
PROC_USART1_TX: U1.30, U4.7
RST_OUT_U3_JTAG_RST_B: R9.1, U3.10, U12.1
VCC_S1_6V2: C23.1, C26.1, C27.1, J1.1, R13.2, U8.4
VCC_TIER1_3V3: C1.1, C2.1, C3.1, C4.1, C5.1, C6.1, C7.1, C14.1, C15.1, C16.1, C17.1, C24.1, C25.1, C28.1, C29.1, F1.2, R1.2, R3.2, R4.2, R6.2, R7.2, R8.2, R9.2, R10.2, R11.2, R14.1, R16.2, R17.2, R19.1, U1.1, U1.24, U1.36, U1.48, U2.8, U3.1, U4.12, U4.19, U8.5, U9.6, U12.5, U13.5
